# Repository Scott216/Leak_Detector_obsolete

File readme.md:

This project detects water and sends out  Tweet if water is detected.  The main boards is an Arduino Leonardo with an Ethernet Shield.  The moisture sensors are hard-wired to the PCB.  When hard wiring is not practical, it uses a couple of Panstamps which provide wireless communication.  A Panstamp is basically and Arduino Pro-mini with a wireless radio.  

I chose Leonardo because I needed an Arduino without the headers installed.  The Ethernet shield is actually soldered to the Leonardo with the Ethernet Shield's pins sticking through the Leonardo.  They are still plenty long enough so the Leonardo/Ethernet sandwich can be plugged into the headers on the PCB.

To make the water detector sensor, take a dried out sponge and insert two 14 GA solid copper wires, about an inch apart.  I like to cut copper wire at an angle so it forms a sharp point - this makes it easier to insert into the sponge.  Use small gauge stranded wire to connect the sponge to terminal strip. When sponge is dry it appears as an open circuit. When wet it's varies from 30k to 300k ohms.  I have [sample op-amp circuit](https://www.circuitlab.com/circuit/ayhr2v/water-detector-v2/) circuitlab.com.

Use a MCP6004 Op Amp. Need the Op-amp because the impedance of the sponge is high and you get false readings if you wire directly to an Arduino. I'm using the op amp as a comparator.

Main board leak detector BOM

    1x OKW Enclosure B6504112 $9.77
        PCB Board specs 3.87" x 3.22". position screw terminal holes 0.27" from edge
        2x M2.5 x 6mm Screws to mount PCB to OKW Enclosure
        2x 18 position plug header, PCB Side CTB9358/18AO $2.14
        2x 18 Position screw terminal CTB9208/18 $5.84 
    1x Arduino Leonardo - without headers
    1x Ethernet Shield]
    1x panStamp - http://www.panstamp.com/products/wirelessarduino
    1x JST PH 5-position header P/N B5B-PH-K-S, Digikey 455-1707-ND for OLED Display, (JST Data Sheet)
    1x JST PH 5-wire cable Sparkfun PRT-09917, JST # PHR-5, Crimp pin SPH-002T-P0.5S
    1x JST PH 4-position header P/N B4B-PH-K-S, Digikey 455-1706-ND for LEDs
    1x JST PH 4-wire cable Sparkfun PRT-09916, JST # PHR-4, Crimp pin SPH-002T-P0.5S
    1x JST PH 2-position header P/N B2B-PH-K-S, Digikey 455-1704-ND for on-off switch
    1x JST PH 2-wire cable Sparkfun PRT-09914, JST # PHR-2, Crimp pin SPH-002T-P0.5S
    1x OLED 128 x 32 I2C Display, Adafruit 931
    1x Reed Relay, Hamlin HE751A0510, Digikey HE124-ND
    3x MCP6004 Op amp Digikey MCP6004-I/P-ND
    3x Resistor network 1MΩ Bourns P/N 4606X-101-105LF, Digikey 4606X-1-105LF-ND. (cut off lead on pin 6)
    2x 330Ω 1/4 watt resistors
    2x 4.7kΩ 1/4 watt resistors
    2x 68Ω 1/4 watt resistors
    1x 150Ω 1/4 watt resistor
    1x 10k trimmer Pot,Digikey 490-2856-ND
    1x On-Off Switch, CW Industries P/N GPB040B05BR, Digikey SW632-ND
    1x Yellow LED 2 volts, 20 mA, Bivar P/N PM3YDW12.0, Digikey 492-1617-ND
    1x Red LED 2.1 volts, 20 mA, Bivar P/N PM3RDW12.0, Digikey 492-1616-ND
    1x Green LED 2.1 volts, 20 mA, Bifar P/N PM3GDW12.0, Digikey 492-1612-ND
    1x 10-pin Header for Leonardo, Digikey S7043-ND
    2x 8-pin Header for Leonardo, Digikey S7041-ND
    1x 6-pin Header for Leonardo, Digikey S7039-ND
    2x 12-pin Headers for panStamp, Digikey S7045-ND 

Remote Wireless Detector BOM

    1 MCP601 Op Amp Digikey MCP601-I/P-ND
    8 pin DIP socket Sparkfun PRT-07937
    2 Battery Holders, Digikey 708-1412-ND
    2 CR123 batteries
    1 470k ohm resistor
    1 Panstamp
    1 slide switch Sparkfun COM-00102
    2 5.6 ohm resistor for green & blue led in RGB LED
    1 68 ohm resistor for for red in RGB LED
    1 RGB LED Sparkfun COM-00105
    1 Pushbutton switch, Sparkfun COM-00097
    1 OneWire temp sensor DS18B20
    2 12-pin headers for PanStamp

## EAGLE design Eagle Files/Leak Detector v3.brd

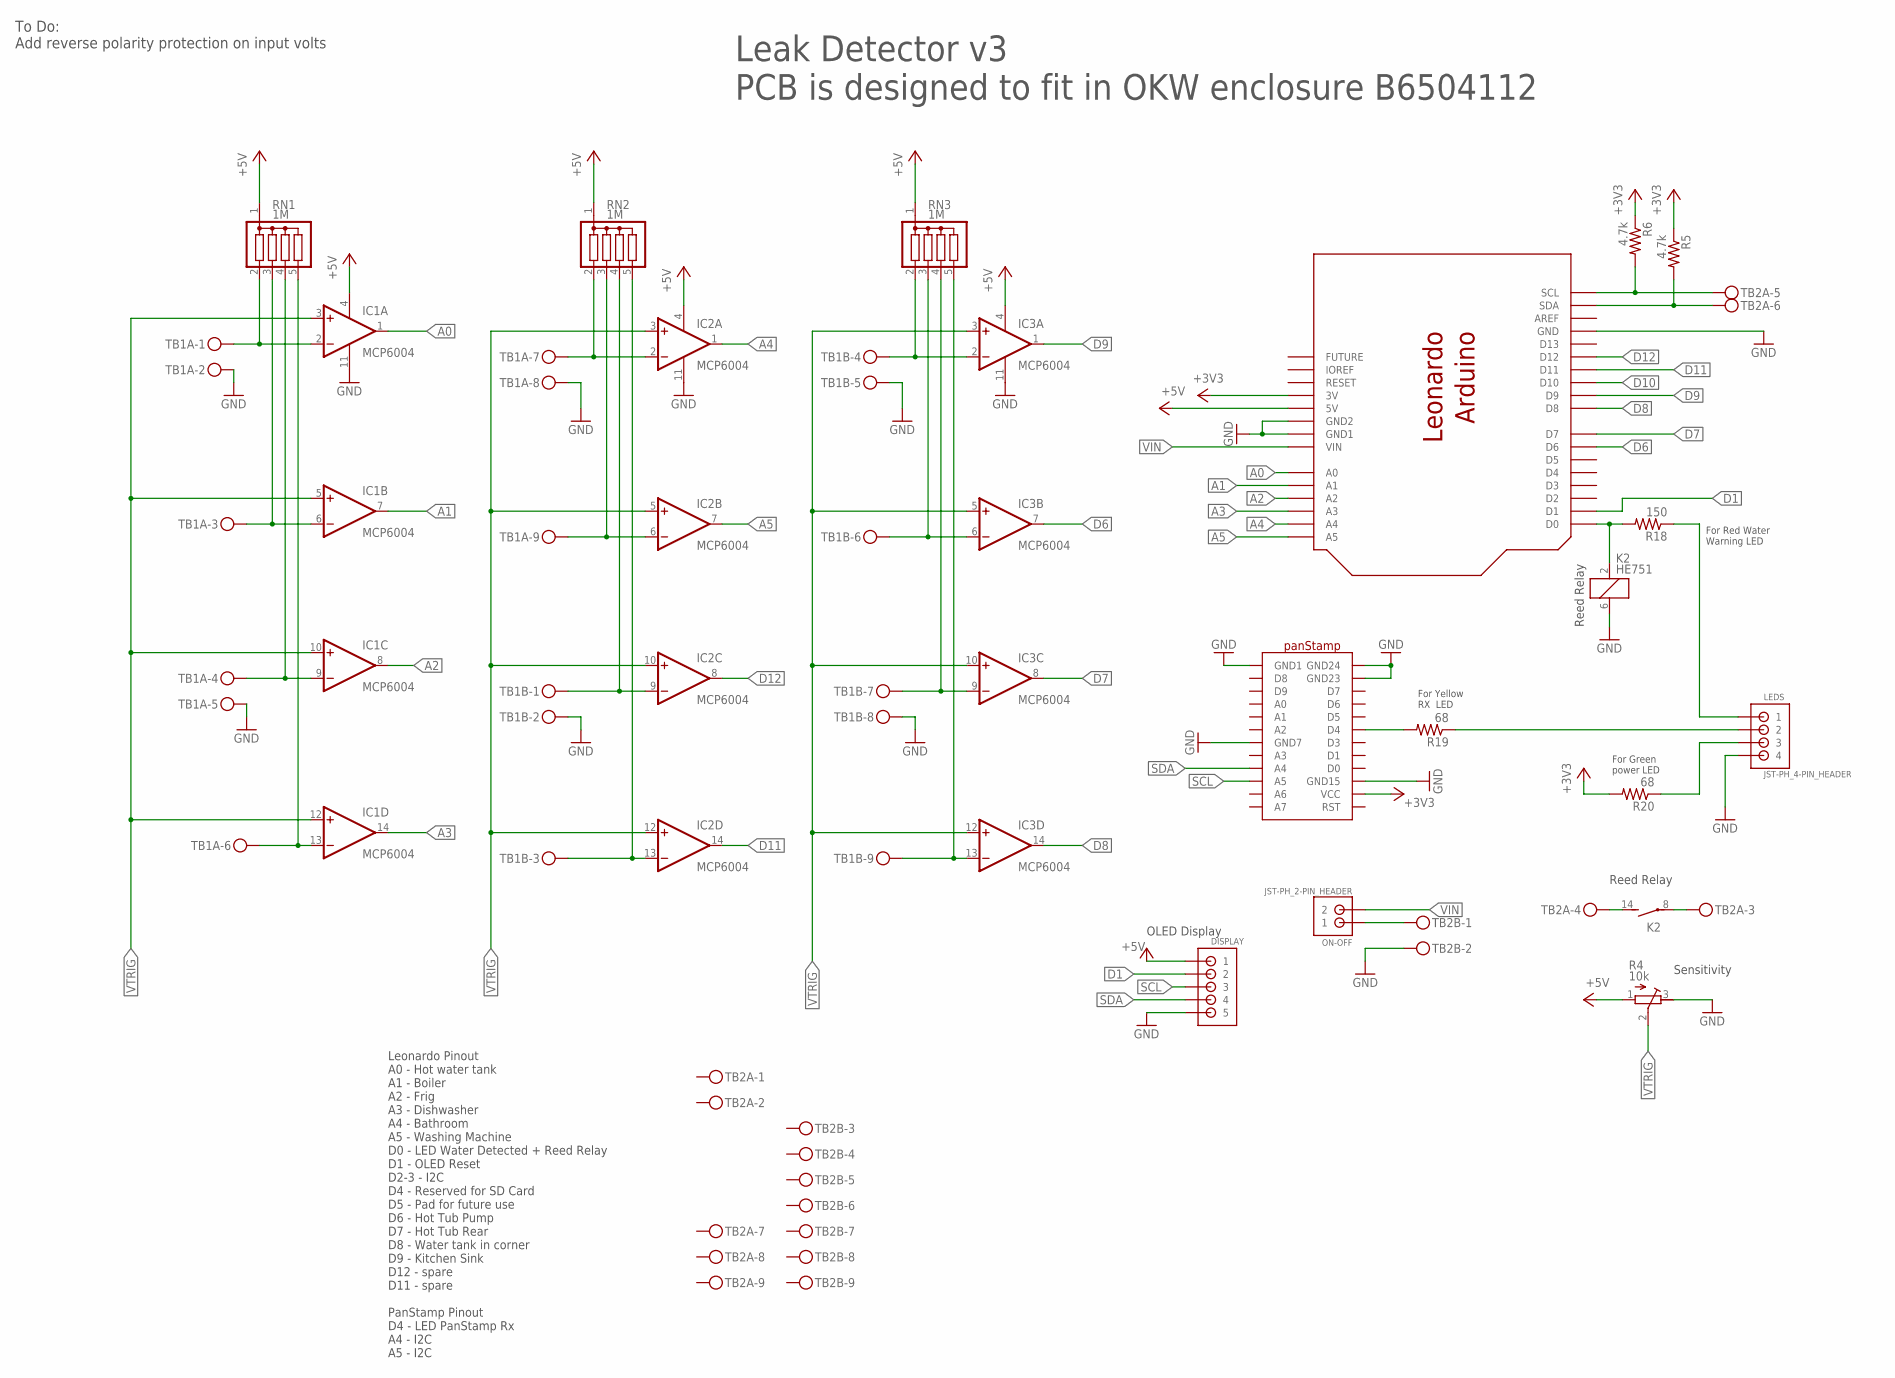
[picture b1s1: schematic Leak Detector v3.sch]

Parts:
DISPLAY: JST-PH_5-PIN_HEADER; JST_B5B-PH_HEADER
IC1, IC2, IC3: MCP6004; DIL14
K2: HE751
LEDS: JST-PH_4-PIN_HEADER; JST_B4B-PH_HEADER
ON-OFF: JST-PH_2-PIN_HEADER; JST_B2B-PH_HEADER
R4: 10k; RTRIM3296P
R5, R6: 4.7k; 0207/10
R18: 150; 0207/10
R19, R20: 68; 0207/10
RN1, RN2, RN3: 1M; SIL5
TB1A, TB1B, TB2A, TB2B: MKDSN1,5/9-5,08
U$1: ARDUINO_LEONARDO
U$2: PANSTAMP

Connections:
+3V3: R5.1, R6.1, R20.2, U$1.3V, U$2.VCC
+5V: DISPLAY.P1 (1), IC1.4 (V+), IC2.4 (V+), IC3.4 (V+), R4.1 (E), RN1.1, RN2.1, RN3.1, U$1.5V
A0: IC1.1 (OUT), U$1.A0
A1: IC1.7 (OUT), U$1.A1
A2: IC1.8 (OUT), U$1.A2
A3: IC1.14 (OUT), U$1.A3
A4: IC2.1 (OUT), U$1.A4
A5: IC2.7 (OUT), U$1.A5
BATHROOM: IC2.2 (-IN), RN2.2, TB1A.7
BOILER: IC1.6 (-IN), RN1.3, TB1A.3
D1: DISPLAY.P2 (2), U$1.D1
D6: IC3.7 (OUT), U$1.D6
D7: IC3.8 (OUT), U$1.D7
D8: IC3.14 (OUT), U$1.D8
D9: IC3.1 (OUT), U$1.D9
D10: U$1.D10
D11: IC2.14 (OUT), U$1.D11
D12: IC2.8 (OUT), U$1.D12
DISHWASHER: IC1.13 (-IN), RN1.5, TB1A.6
FRIG: IC1.9 (-IN), RN1.4, TB1A.4
GND: DISPLAY.P5 (5), IC1.11 (V-), IC2.11 (V-), IC3.11 (V-), K2.6 (2), LEDS.P4 (4), R4.3 (A), TB1A.2, TB1A.5, TB1A.8, TB1B.2, TB1B.5, TB1B.8, TB2B.2, U$1.GND, U$1.GND$2 (GND2), U$1.GND$3 (GND1), U$2.GND1, U$2.GND7, U$2.GND15, U$2.GND23, U$2.GND24
HAVEPOWER: LEDS.P3 (3), R20.1
HOT_TUB_PUMP: IC3.6 (-IN), RN3.3, TB1B.6
HOT_TUB_REAR: IC3.9 (-IN), RN3.4, TB1B.7
HOT_WATER_TANK: IC1.2 (-IN), RN1.2, TB1A.1
ISWATER: LEDS.P1 (1), R18.1
unnamed: ON-OFF.P1 (1), TB2B.1
unnamed: K2.2 (1), R18.2, U$1.D0
unnamed: K2.14 (S), TB2A.4
unnamed: K2.8, TB2A.3
unnamed: R19.2, U$2.D4
RXOK: LEDS.P2 (2), R19.1
SCL: DISPLAY.P3 (3), R6.2, TB2A.5, U$1.SCL, U$2.A5
SDA: DISPLAY.P4 (4), R5.2, TB2A.6, U$1.SDA, U$2.A4
SINK: IC3.2 (-IN), RN3.2, TB1B.4
SPARE1: IC2.9 (-IN), RN2.4, TB1B.1
SPARE2: IC2.13 (-IN), RN2.5, TB1B.3
VIN: ON-OFF.P2 (2), U$1.VIN
VTRIG: IC1.3 (+IN), IC1.5 (+IN), IC1.10 (+IN), IC1.12 (+IN), IC2.3 (+IN), IC2.5 (+IN), IC2.10 (+IN), IC2.12 (+IN), IC3.3 (+IN), IC3.5 (+IN), IC3.10 (+IN), IC3.12 (+IN), R4.2 (S)
WASH_MACH: IC2.6 (-IN), RN2.3, TB1A.9
WATER_TANK: IC3.13 (-IN), RN3.5, TB1B.9

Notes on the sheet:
Leonardo Pinout A0 - Hot water tank A1 - Boiler A2 - Frig A3 - Dishwasher A4 - Bathroom A5 - Washing Machine D0 - LED Water Detected + Reed Relay D1 - OLED Reset D2-3 - I2C D4 - Reserved for SD Card D5 - Pad for future use D6 - Hot Tub Pump D7 - Hot Tub Rear D8 - Water tank in corner D9 - Kitchen S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
Leak Detector v3 PCB is designed to fit in OKW enclosure B6504112
OLED Display
Reed Relay
Sensitivity
For Green power LED
For Yellow RX LED
For Red Water Warning LED
To Do: Add reverse polarity protection on input volts

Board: 2 copper layers, 22 parts (0 on the bottom side), 40 nets, no tracks yet.

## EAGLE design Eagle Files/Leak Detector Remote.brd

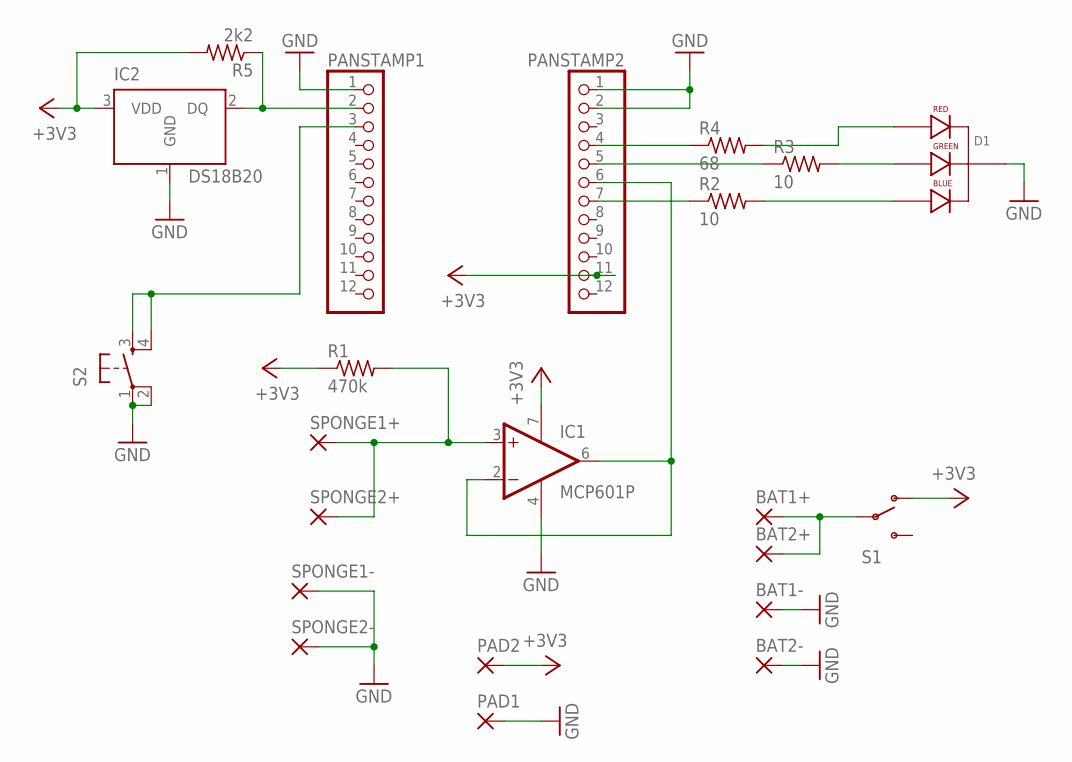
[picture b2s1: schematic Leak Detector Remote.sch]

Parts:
BAT1+, BAT1-, BAT2+, BAT2-: 3,81/1,4
D1: LED-RGB-CC-THRUCLEAR; LED-RGB-THRU
IC1: MCP601P; DIL08
IC2: DS18B20; TO-92
PAD1, PAD2: 1,6/0,9
PANSTAMP1, PANSTAMP2: PINHD-1X12; 1X12
R1: 470k; 0204/7
R2, R3: 10; 0204/7
R4: 68; 0204/7
R5: 2k2; 0204/7
S1: SWITCH-SPDTKIT; SWITCH-SPDT_KIT
S2: TAC_SWITCHPTH; TACTILE-PTH
SPONGE1+, SPONGE1-, SPONGE2+, SPONGE2-: 3,81/1,4

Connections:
+3V3: IC1.7 (V+), IC2.3 (VDD), PAD2.1, PANSTAMP2.11, R1.1, R5.2, S1.1 (O)
D3: PANSTAMP2.7, R2.1
D4: IC1.2 (-IN), IC1.6 (OUT), PANSTAMP2.6
D5: PANSTAMP2.5, R3.1
D6: PANSTAMP2.4, R4.1
D8: IC2.2 (DQ), PANSTAMP1.2, R5.1
D9: PANSTAMP1.3, S2.3, S2.4
GND: BAT1-.1, BAT2-.1, D1.2 (CATHODE), IC1.4 (V-), IC2.1 (GND), PAD1.1, PANSTAMP1.1, PANSTAMP2.1, PANSTAMP2.2, S2.1, S2.2, SPONGE1-.1, SPONGE2-.1
unnamed: IC1.3 (+IN), R1.2, SPONGE1+.1, SPONGE2+.1
unnamed: BAT1+.1, BAT2+.1, S1.2
unnamed: D1.1 (RED_CATHODE), R4.2
unnamed: D1.3 (GREEN_CATHODE), R3.2
unnamed: D1.4 (BLUE_CATHODE), R2.2

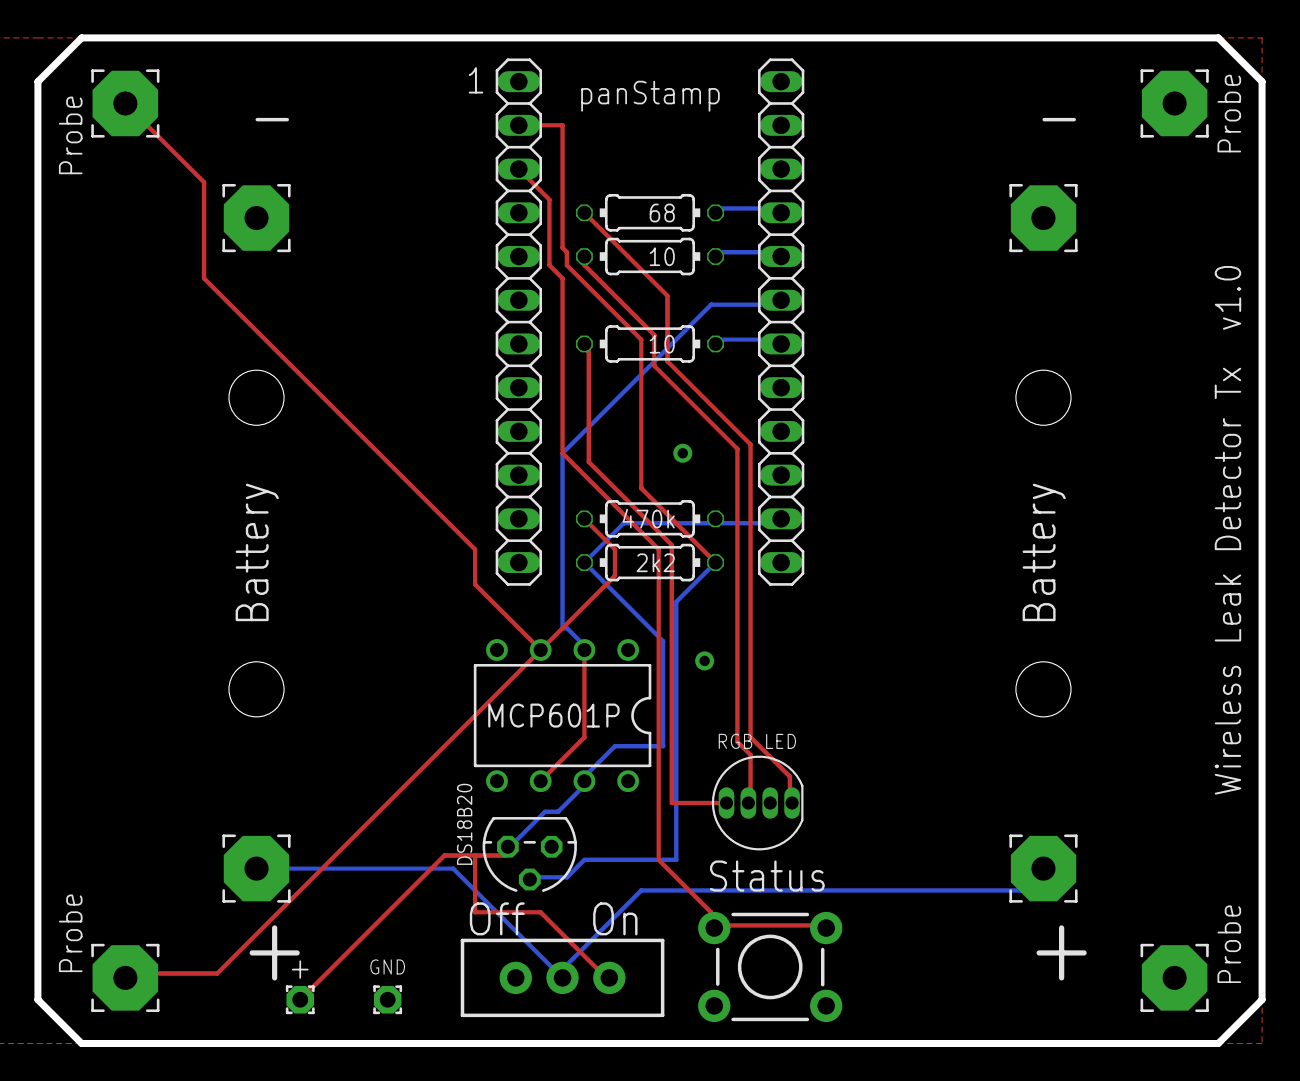
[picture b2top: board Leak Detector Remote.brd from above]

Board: 2 copper layers, 71.1 x 58.4 mm, 22 parts (0 on the bottom side), 13 nets.

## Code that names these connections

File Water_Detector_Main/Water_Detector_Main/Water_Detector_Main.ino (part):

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#define HOTTUBFILTER        6   // Sponge in crawlspace by hot tub filter and pump
#define HOTTUBBACK          7   // Sponge in crawlspace behind hot tub
#define WATERTANK           8   // Sponge in crawlspace corner by water tank
#define KITCHENSINK         9   // Sponge under kitchen sink
// reserved                10   // Slave select
#define DEHUMIDIFIER       11   // Dehumidifier
#define TBD1               12   // Future Use
#define WATERHEATER        A0   // Sponge under hot water heater
#define BOILER             A1   // Sponge next to boiler
#define FRIG               A2   // Sponge behind refrigerator
#define DISHWASHER         A3   // Sponge behind dishwasher
#define FIRSTFLOORBRSINK   A4   // Sponge in first floor bathroom sink
#define WASHINGMACH        A5   // Sponge next to washing machine

#define WET HIGH       // When a sponge is wet, the digital input is HIGH
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
const uint8_t ADDR_I2C_OLED  =     0x3C;  // OLED Display I2C address
const uint8_t ADDR_I2C_SLAVE =       21;  // I2C Slave address of panStamp Rx
const uint8_t ADDR_BATH_MASTER =      0;  // panStamp device address for 2nd floor master bathroom  // SRG: Change addresses to 0,1,2
const uint8_t ADDR_BATH_GUEST =       1;  // panStamp device address for 2nd floor guest bathroom
const uint8_t ADDR_BATH_FIRST =       2;  // panStamp device address for 1st floor bathroom
const uint8_t NUM_SENSORS_WIRELESS =  3;  // number of wireless water sensors
const uint8_t NUM_SENSORS_WIRED =    12;  // Number of wired water detector inputs
const uint8_t DATA_LENGTH_I2C =      10;  // Packets sent by each panStamp
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Twitter twitter(TWITTER_TOKEN);

// Put input pin numbers in array so you can use loops to read wired inputs
uint8_t InputPinNum[] = { FIRSTFLOORBRSINK, WASHINGMACH, TBD1, DEHUMIDIFIER, WATERHEATER, BOILER, FRIG, DISHWASHER, KITCHENSINK, HOTTUBFILTER, HOTTUBBACK, WATERTANK };


// Function Prototypes
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
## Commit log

2013-10-25 enabled red LED output and reed relay
2013-12-13 alert when remote sensor comes back online
2013-12-18 char twitterMsg[] was too short
2014-01-17 Added photos
2014-01-17 Tx Photos
2014-01-17 Eagle Files
2014-01-17 New Readme
2014-01-17 Updated Readme files
2014-01-17 Added readme detail
2014-01-17 Formatting readme
2014-01-17 formatting
2014-01-24 EmbedXcode+ upgrade
    Changes resulting from EmbedXcode upgrade
2014-01-26 Took out hyperlink to OKW
2014-01-26 Took out some hyperlinks
2014-02-18 Added time and DoW to OLED
    Heartbeat was 3 days off. Added time to display to monitor
2014-02-24 Moved static variables
    Put static variables inside functions instead of making them global
2014-07-06 Added checksum
2014-07-06 Changed NTP time update
2015-01-04 v2.05 minor changes
2015-01-04 Removed files
2015-01-04 code to get rid of invalid compiler warnings
2015-02-14 v2.0 - Comment changes
2015-02-14 v2.08 Fixed heartbeat, added dehumidifier sensor
    Fixed Sunday heartbeat alert
    Added a dehumidifier sensor to one of the two spare wired inputs
2015-02-14 Eagle board files
2015-02-14 v2.09 - removed PrintStates() function
    Don’t need this anymore, OLED display shows everything needed
2015-03-08 panStamp API upgrade
    Rewrite to work with latest API and panStamp IDE 1.6.0 patch. Lots of
    changes.
2015-03-09 v3.0 - major changes
    Changed I2C so it requested data from a specific wireless leak
    detector. Previously the slave sent data for two detectors in one
    packet. But now that I have three, I decided to change it. Data is
    also stored in a structure array.
2015-03-09 Removed unused files
2015-03-09 noted I2C packet structure change
2015-03-09 v2.03 used an array of structures
2015-03-09 v2.02 changed Tx address range
2015-03-23 v2.04 added some print statements
2015-03-23 v3.01 - minor clean up
2015-03-23 v2.04 - minor changes

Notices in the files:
parts and their libraries:
SparkFun-Electromechanical: Licensing: CC v3.0 Share-Alike You are welcome to use this library for commercial purposes.
